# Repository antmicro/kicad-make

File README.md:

# KiCad Make (kmake)

Copyright (c) 2019-2026 [Antmicro](https://www.antmicro.com)

This is a simple utility that automates handling of [KiCad](https://www.kicad.org/) projects.
`kmake` provides a unified way to generate KiCad production files and manage project structure.
The script can be used locally and in conjunction with CI infrastructure.
`kmake` primarily targets KiCad 9 projects (supporting also KiCad 8-10).
It uses the KiCad CLI where possible and [askiff](https://github.com/antmicro/askiff) for functions that require raw file manipulation.

> KiCad 8 files should be fully supported (they will be upgraded on fly), however this has not been extensively tested.

## Documentation

Visit the [`kmake` documentation](https://antmicro.github.io/kicad-make/) for more information about usage and development of `kmake`.

## Installation

### Requirements

`kmake` depends on the following packages:

* `KiCad 9.0.x`
* `python >= 3.11`

### Installation (Debian)

1. Install requirements

    ```bash
    sudo apt install kicad python3 pipx
    pipx ensurepath
    ```

2. Clone and install `kmake` repository:

    ```bash
    pipx install 'git+https://github.com/antmicro/kicad-make.git'
    ```

## Usage

> Important: All commands should be issued from the KiCad project root directory.

To show available functionalities run:

```bash
cd <KiCad project directory>
kmake --help
```

## Version

As an convention, the `kmake` version is derived from the `KiCad` version supported by the release.
For example, `kmake` version `9.0.x` supports `KiCad` version `9.0.x`.

To check which version of `kmake` is installed in your system, run:

```bash
kmake version
```

## Licensing

This project is licensed under the [Apache-2.0](LICENSE) license.

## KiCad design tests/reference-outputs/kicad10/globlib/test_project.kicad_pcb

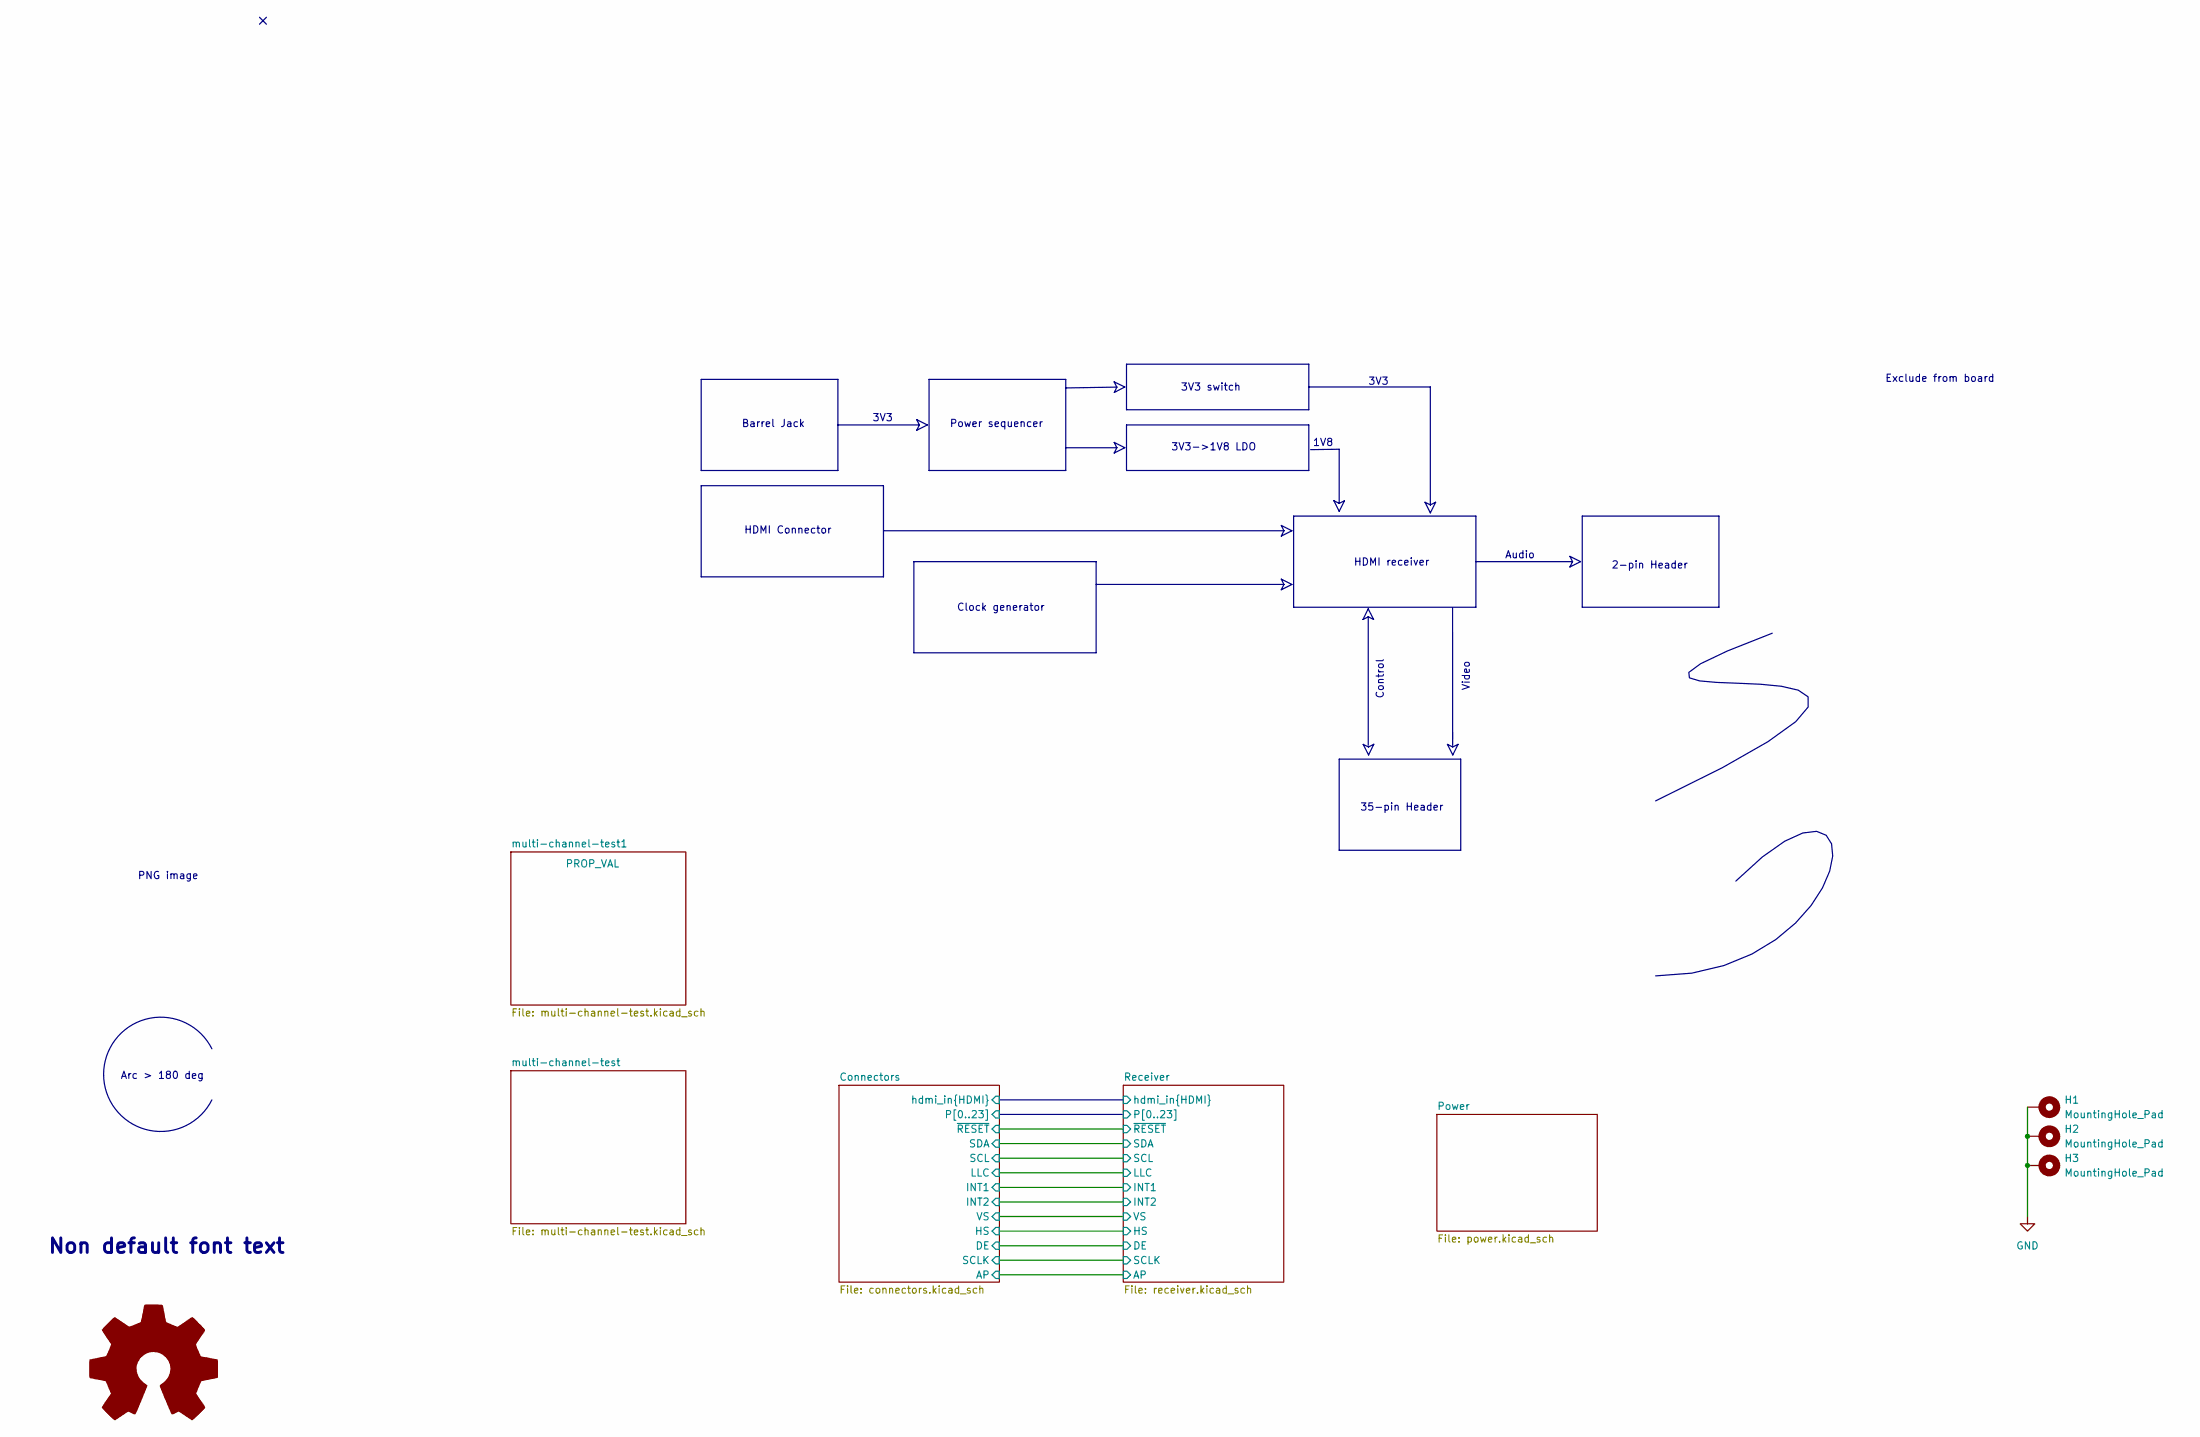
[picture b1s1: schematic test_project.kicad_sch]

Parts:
H1, H2, H3: MountingHole_Pad

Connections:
GND: H1.1, H2.1, H3.1; also elsewhere on the board

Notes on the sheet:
Control
Arc > 180 deg
PNG image
3V3
Video
1V8
Exclude from board
Audio
3V3 switch
Power sequencer
2-pin Header
35-pin Header
3V3->1V8 LDO
Barrel Jack
Non default font text
Clock generator
HDMI Connector
HDMI receiver

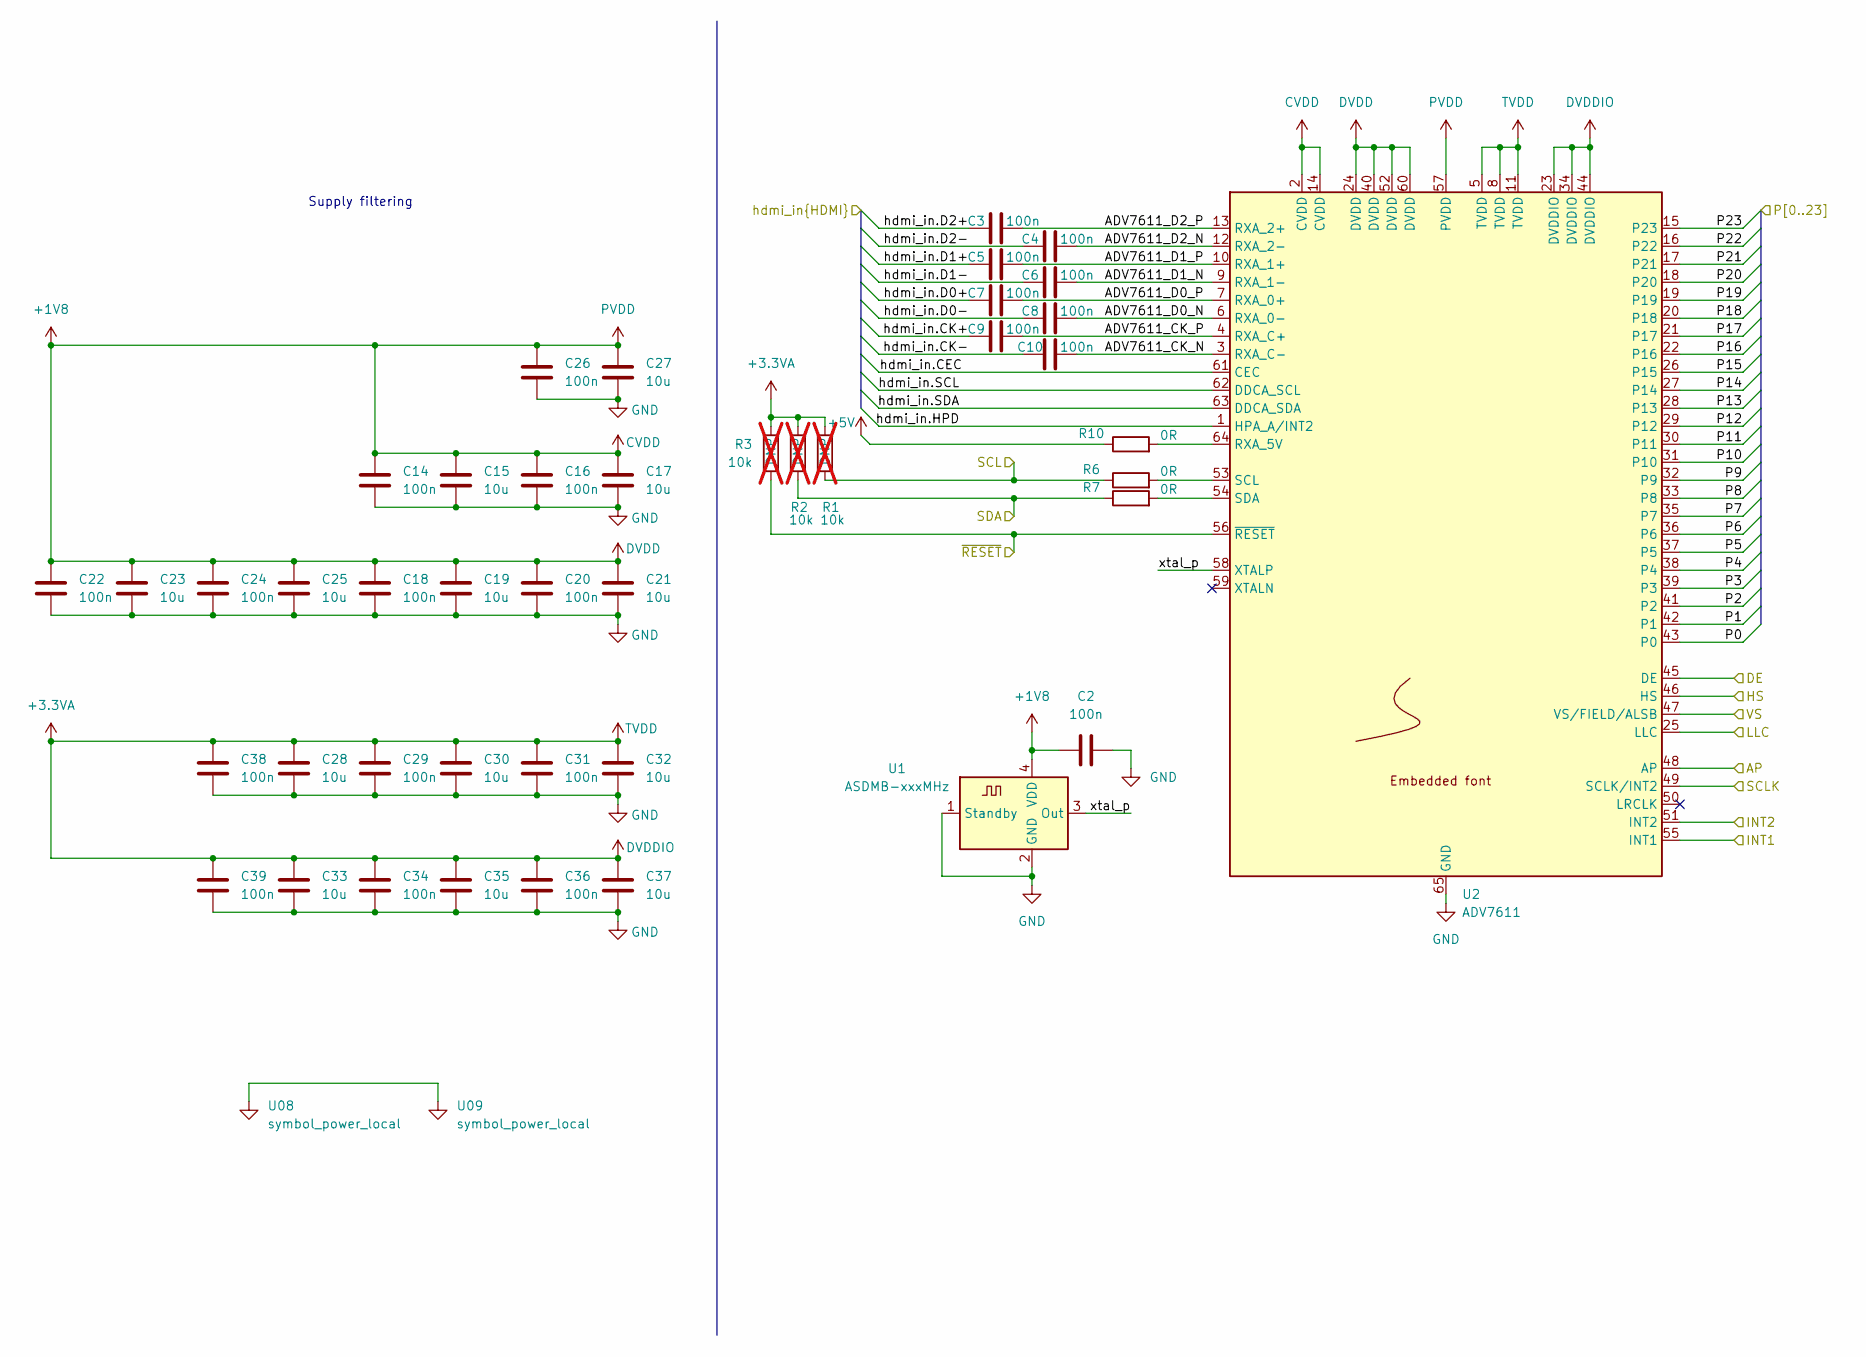
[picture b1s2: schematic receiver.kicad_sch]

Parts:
C2, C3, C4, C5, C6, C7, C8, C9, C10, C14, C16, C18, C20, C22, C24, C26, C29, C31, C34, C36, C38, C39: 100n
C15, C17, C19, C21, C23, C25, C27, C28, C30, C32, C33, C35, C37: 10u
R1, R2, R3: 10k; not fitted
R6, R7, R10: 0R
U1: ASDMB-xxxMHz; Oscillator_SMD_Abracon_ASDMB-4Pin_2.5x2.0mm; MPN ASDMB-28.6363MHz-XY
U2: ADV7611; LQFP-64-1EP_10x10mm_P0.5mm_EP5x5mm
U08, U09: symbol_power_local

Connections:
+1V8: C2.2, C14.1, C15.1, C16.1, C17.1, C18.1, C19.1, C20.1, C21.1, C22.1, C23.1, C24.1, C25.1, C26.1, C27.1, U1.4 (VDD), U2.2 (CVDD), U2.14 (CVDD), U2.24 (DVDD), U2.40 (DVDD), U2.52 (DVDD), U2.57 (PVDD), U2.60 (DVDD); also elsewhere on the board
+3.3VA: C28.1, C29.1, C30.1, C31.1, C32.1, C33.1, C34.1, C35.1, C36.1, C37.1, C38.1, C39.1, R1.1, R2.1, R3.1, U2.5 (TVDD), U2.8 (TVDD), U2.11 (TVDD), U2.23 (DVDDIO), U2.34 (DVDDIO), U2.44 (DVDDIO); also elsewhere on the board
+5V: R10.1; also elsewhere on the board
/Connectors/AP: U2.48 (AP); also elsewhere on the board
/Connectors/DE: U2.45 (DE); also elsewhere on the board
/Connectors/HS: U2.46 (HS); also elsewhere on the board
/Connectors/INT1: U2.55 (INT1); also elsewhere on the board
/Connectors/INT2: U2.51 (INT2); also elsewhere on the board
/Connectors/LLC: U2.25 (LLC); also elsewhere on the board
/Connectors/P0: U2.43 (P0); also elsewhere on the board
/Connectors/P1: U2.42 (P1); also elsewhere on the board
/Connectors/P2: U2.41 (P2); also elsewhere on the board
/Connectors/P3: U2.39 (P3); also elsewhere on the board
/Connectors/P4: U2.38 (P4); also elsewhere on the board
/Connectors/P5: U2.37 (P5); also elsewhere on the board
/Connectors/P6: U2.36 (P6); also elsewhere on the board
/Connectors/P7: U2.35 (P7); also elsewhere on the board
/Connectors/P8: U2.33 (P8); also elsewhere on the board
/Connectors/P9: U2.32 (P9); also elsewhere on the board
/Connectors/P10: U2.31 (P10); also elsewhere on the board
/Connectors/P11: U2.30 (P11); also elsewhere on the board
/Connectors/P12: U2.29 (P12); also elsewhere on the board
/Connectors/P13: U2.28 (P13); also elsewhere on the board
/Connectors/P14: U2.27 (P14); also elsewhere on the board
/Connectors/P15: U2.26 (P15); also elsewhere on the board
/Connectors/P16: U2.22 (P16); also elsewhere on the board
/Connectors/P17: U2.21 (P17); also elsewhere on the board
/Connectors/P18: U2.20 (P18); also elsewhere on the board
/Connectors/P19: U2.19; also elsewhere on the board
/Connectors/P20: U2.18 (P20); also elsewhere on the board
/Connectors/P21: U2.17 (P21); also elsewhere on the board
/Connectors/P22: U2.16 (P22); also elsewhere on the board
/Connectors/P23: U2.15 (P23); also elsewhere on the board
/Connectors/SCL: R1.2, R6.1; also elsewhere on the board
/Connectors/SCLK: U2.49 (SCLK/INT2); also elsewhere on the board
/Connectors/SDA: R2.2, R7.1; also elsewhere on the board
/Connectors/VS: U2.47 (VS/FIELD/ALSB); also elsewhere on the board
/Connectors/hdmi_in.CEC: U2.61 (CEC); also elsewhere on the board
/Connectors/hdmi_in.CK+: C9.1; also elsewhere on the board
/Connectors/hdmi_in.CK-: C10.1; also elsewhere on the board
/Connectors/hdmi_in.D0+: C7.1; also elsewhere on the board
/Connectors/hdmi_in.D0-: C8.1; also elsewhere on the board
/Connectors/hdmi_in.D1+: C5.1; also elsewhere on the board
/Connectors/hdmi_in.D1-: C6.1; also elsewhere on the board
/Connectors/hdmi_in.D2+: C3.1; also elsewhere on the board
/Connectors/hdmi_in.D2-: C4.1; also elsewhere on the board
/Connectors/hdmi_in.HPD: U2.1 (HPA_A/INT2); also elsewhere on the board
/Connectors/hdmi_in.SCL: U2.62 (DDCA_SCL); also elsewhere on the board
/Connectors/hdmi_in.SDA: U2.63 (DDCA_SDA); also elsewhere on the board
/Connectors/~RESET: R3.2, U2.56 (~RESET); also elsewhere on the board
/Receiver/ADV7611_CK_N: C10.2, U2.3 (RXA_C-)
/Receiver/ADV7611_CK_P: C9.2, U2.4 (RXA_C+)
/Receiver/ADV7611_D0_N: C8.2, U2.6 (RXA_0-)
/Receiver/ADV7611_D0_P: C7.2, U2.7 (RXA_0+)
/Receiver/ADV7611_D1_N: C6.2, U2.9 (RXA_1-)
/Receiver/ADV7611_D1_P: C5.2, U2.10 (RXA_1+)
/Receiver/ADV7611_D2_N: C4.2, U2.12 (RXA_2-)
/Receiver/ADV7611_D2_P: C3.2, U2.13 (RXA_2+)
/Receiver/xtal_p: U1.3 (Out), U2.58 (XTALP)
GND: C2.1, C14.2, C15.2, C16.2, C17.2, C18.2, C19.2, C20.2, C21.2, C22.2, C23.2, C24.2, C25.2, C26.2, C27.2, C28.2, C29.2, C30.2, C31.2, C32.2, C33.2, C34.2, C35.2, C36.2, C37.2, C38.2, C39.2, U1.1 (Standby), U1.2 (GND), U2.65 (GND); also elsewhere on the board
unnamed: R10.2, U2.64 (RXA_5V)
unnamed: R6.2, U2.53 (SCL)
unnamed: R7.2, U2.54 (SDA)
unnamed: U08., U09.

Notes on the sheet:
Supply filtering

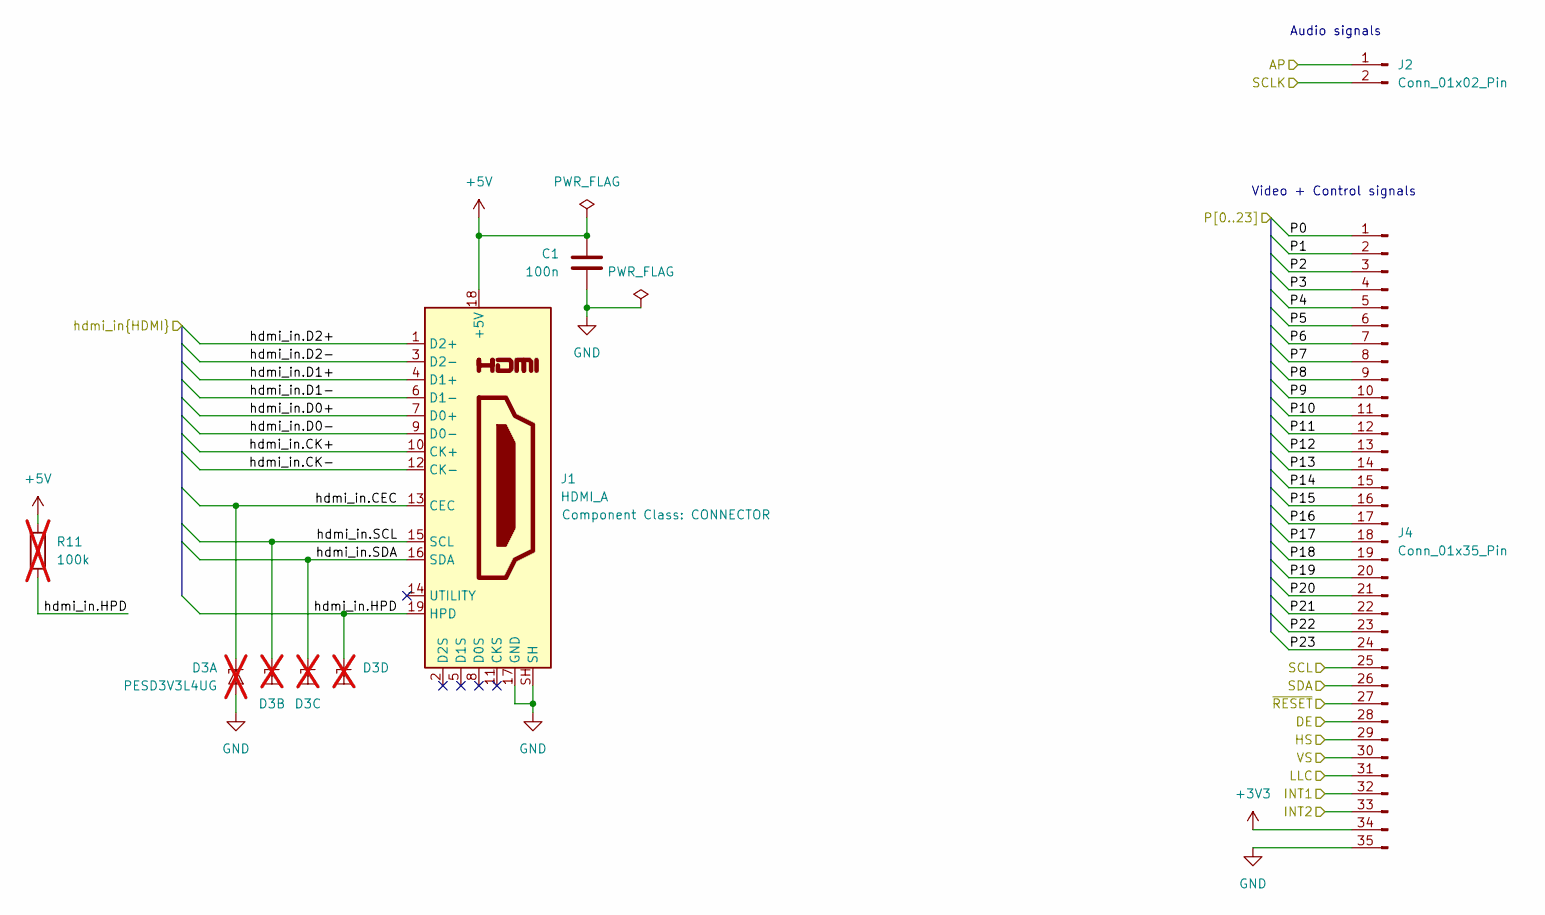
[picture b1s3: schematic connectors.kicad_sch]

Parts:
C1: 100n
D3: PESD3V3L4UG; SOT-353_SC-70-5; not fitted
J1: HDMI_A
J2: Conn_01x02_Pin
J4: Conn_01x35_Pin
R11: 100k; not fitted

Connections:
+3V3: J4.34; also elsewhere on the board
+5V: C1.1, J1.18 (+5V), R11.1; also elsewhere on the board
/Connectors/AP: J2.1; also elsewhere on the board
/Connectors/DE: J4.28; also elsewhere on the board
/Connectors/HS: J4.29; also elsewhere on the board
/Connectors/INT1: J4.32; also elsewhere on the board
/Connectors/INT2: J4.33; also elsewhere on the board
/Connectors/LLC: J4.31; also elsewhere on the board
/Connectors/P0: J4.1; also elsewhere on the board
/Connectors/P1: J4.2; also elsewhere on the board
/Connectors/P2: J4.3; also elsewhere on the board
/Connectors/P3: J4.4; also elsewhere on the board
/Connectors/P4: J4.5; also elsewhere on the board
/Connectors/P5: J4.6; also elsewhere on the board
/Connectors/P6: J4.7; also elsewhere on the board
/Connectors/P7: J4.8; also elsewhere on the board
/Connectors/P8: J4.9; also elsewhere on the board
/Connectors/P9: J4.10; also elsewhere on the board
/Connectors/P10: J4.11; also elsewhere on the board
/Connectors/P11: J4.12; also elsewhere on the board
/Connectors/P12: J4.13; also elsewhere on the board
/Connectors/P13: J4.14; also elsewhere on the board
/Connectors/P14: J4.15; also elsewhere on the board
/Connectors/P15: J4.16; also elsewhere on the board
/Connectors/P16: J4.17; also elsewhere on the board
/Connectors/P17: J4.18; also elsewhere on the board
/Connectors/P18: J4.19; also elsewhere on the board
/Connectors/P19: J4.20; also elsewhere on the board
/Connectors/P20: J4.21; also elsewhere on the board
/Connectors/P21: J4.22; also elsewhere on the board
/Connectors/P22: J4.23; also elsewhere on the board
/Connectors/P23: J4.24; also elsewhere on the board
/Connectors/SCL: J4.25; also elsewhere on the board
/Connectors/SCLK: J2.2; also elsewhere on the board
/Connectors/SDA: J4.26; also elsewhere on the board
/Connectors/VS: J4.30; also elsewhere on the board
/Connectors/hdmi_in.CEC: D3.1 (K1), J1.13 (CEC); also elsewhere on the board
/Connectors/hdmi_in.CK+: J1.10 (CK+); also elsewhere on the board
/Connectors/hdmi_in.CK-: J1.12 (CK-); also elsewhere on the board
/Connectors/hdmi_in.D0+: J1.7 (D0+); also elsewhere on the board
/Connectors/hdmi_in.D0-: J1.9 (D0-); also elsewhere on the board
/Connectors/hdmi_in.D1+: J1.4 (D1+); also elsewhere on the board
/Connectors/hdmi_in.D1-: J1.6 (D1-); also elsewhere on the board
/Connectors/hdmi_in.D2+: J1.1 (D2+); also elsewhere on the board
/Connectors/hdmi_in.D2-: J1.3 (D2-); also elsewhere on the board
/Connectors/hdmi_in.HPD: D3.5 (K4), J1.19 (HPD), R11.2; also elsewhere on the board
/Connectors/hdmi_in.SCL: D3.3 (K2), J1.15 (SCL); also elsewhere on the board
/Connectors/hdmi_in.SDA: D3.4 (K3), J1.16 (SDA); also elsewhere on the board
/Connectors/~RESET: J4.27; also elsewhere on the board
GND: C1.2, D3.2 (A), J1.17 (GND), J1.SH, J4.35; also elsewhere on the board

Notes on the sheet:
Audio signals
Video + Control signals

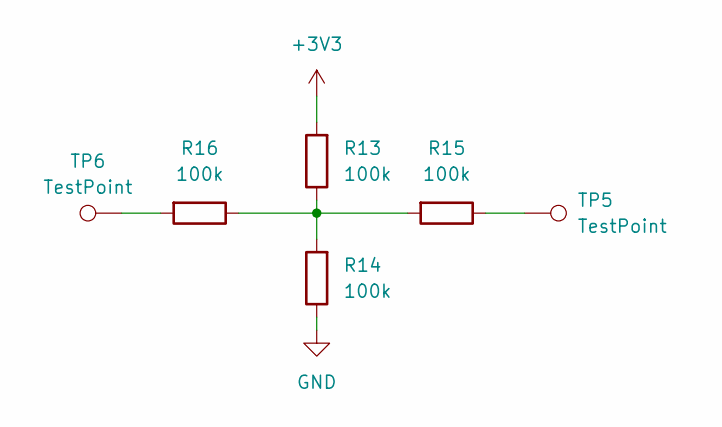
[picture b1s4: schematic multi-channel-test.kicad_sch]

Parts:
R13, R14, R15, R16: 100k
TP5, TP6: TestPoint

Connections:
+3V3: R13.2; also elsewhere on the board
GND: R14.1; also elsewhere on the board
unnamed: R13.1, R14.2, R15.2, R16.1
unnamed: R15.1, TP5.1
unnamed: R16.2, TP6.1

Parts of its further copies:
R17, R18, R19, R20: 100k
TP7, TP8: TestPoint

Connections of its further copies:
+3V3: R18.2; also elsewhere on the board
GND: R19.1; also elsewhere on the board
unnamed: R17.1, R18.1, R19.2, R20.2
unnamed: R17.2, TP7.1
unnamed: R20.1, TP8.1

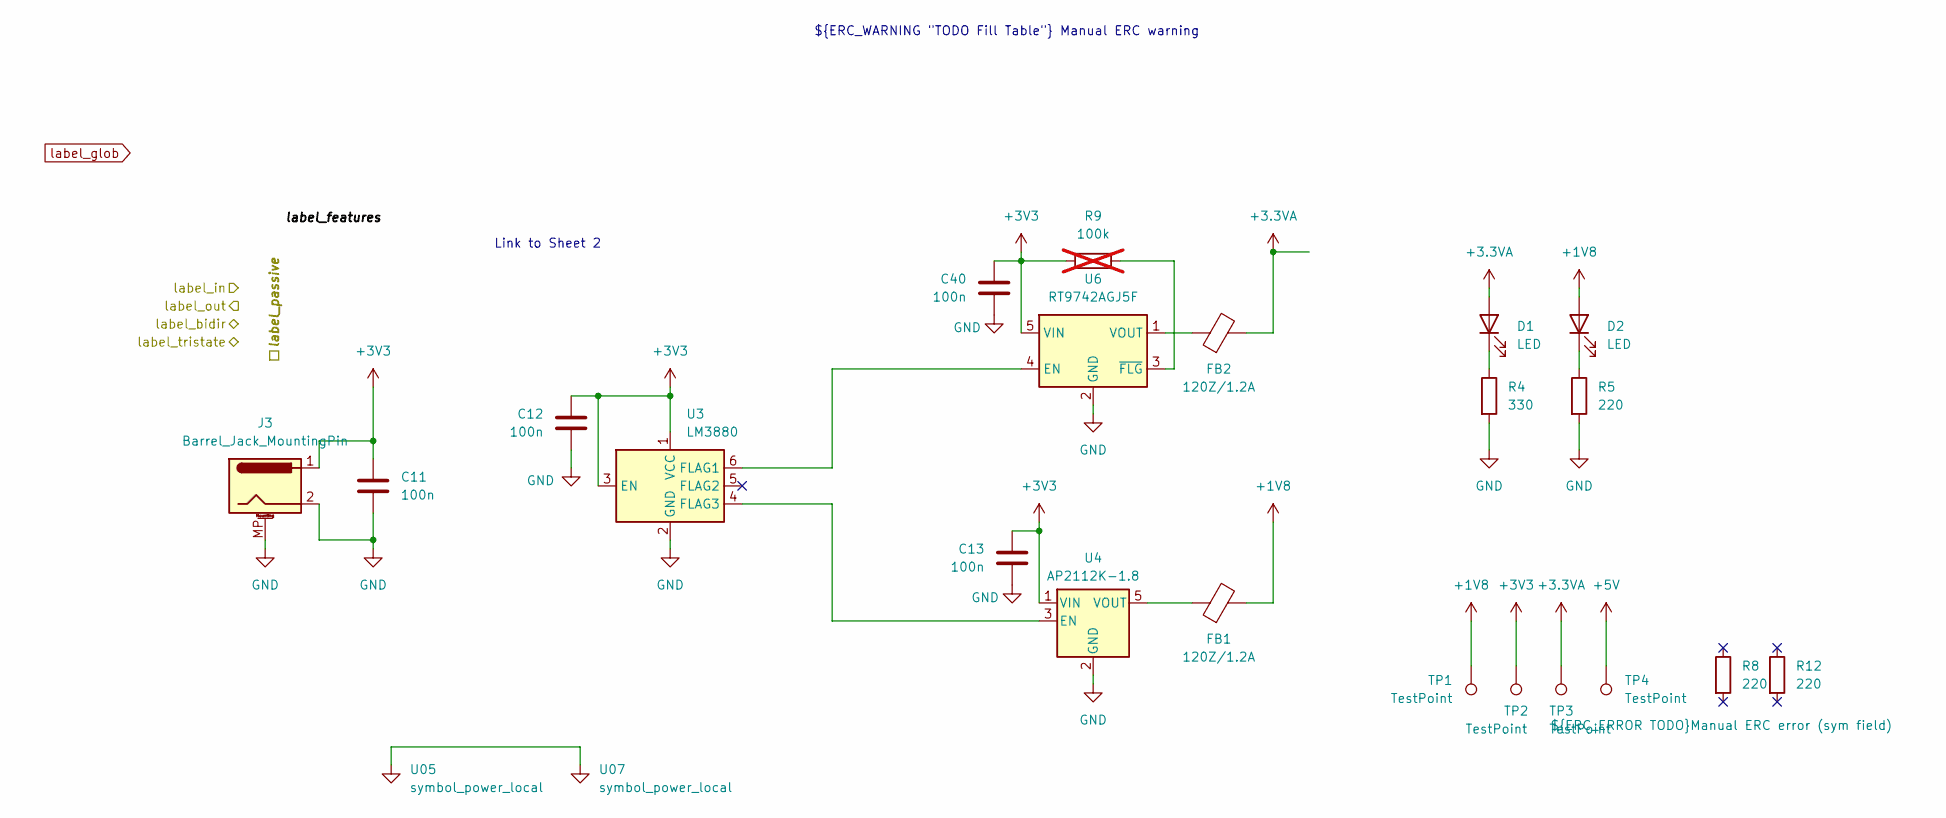
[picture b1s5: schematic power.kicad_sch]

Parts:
C11, C12, C13, C40: 100n
D1, D2: LED
FB1, FB2: 120Z/1.2A
J3: Barrel_Jack_MountingPin
R4: 330
R5, R8, R12: 220
R9: 100k; not fitted
TP1, TP2, TP3, TP4: TestPoint
U3: LM3880; SOT-23-6
U4: AP2112K-1.8; SOT-23-5
U05, U07: symbol_power_local
U6: RT9742AGJ5F; TSOT-23-5

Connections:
+1V8: D2.2 (A), FB1.2, TP1.1; also elsewhere on the board
+3.3VA: D1.2 (A), FB2.2, TP3.1; also elsewhere on the board
+3V3: C11.1, C12.2, C13.2, C40.2, J3.1, R9.1, TP2.1, U3.1 (VCC), U3.3 (EN), U4.1 (VIN), U6.5 (VIN); also elsewhere on the board
+5V: TP4.1; also elsewhere on the board
GND: C11.2, C12.1, C13.1, C40.1, J3.2, J3.MP (MountPin), R4.2, R5.2, U3.2 (GND), U4.2 (GND), U6.2 (GND); also elsewhere on the board
unnamed: D1.1 (K), R4.1
unnamed: D2.1 (K), R5.1
unnamed: U3.6 (FLAG1), U6.4 (EN)
unnamed: U3.4 (FLAG3), U4.3 (EN)
unnamed: FB1.1, U4.5 (VOUT)
unnamed: U05., U07.
unnamed: FB2.1, U6.1 (VOUT)
unnamed: R9.2, U6.3 (~FLG)

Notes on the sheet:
Link to Sheet 2
${ERC_WARNING "TODO Fill Table"} Manual ERC warning

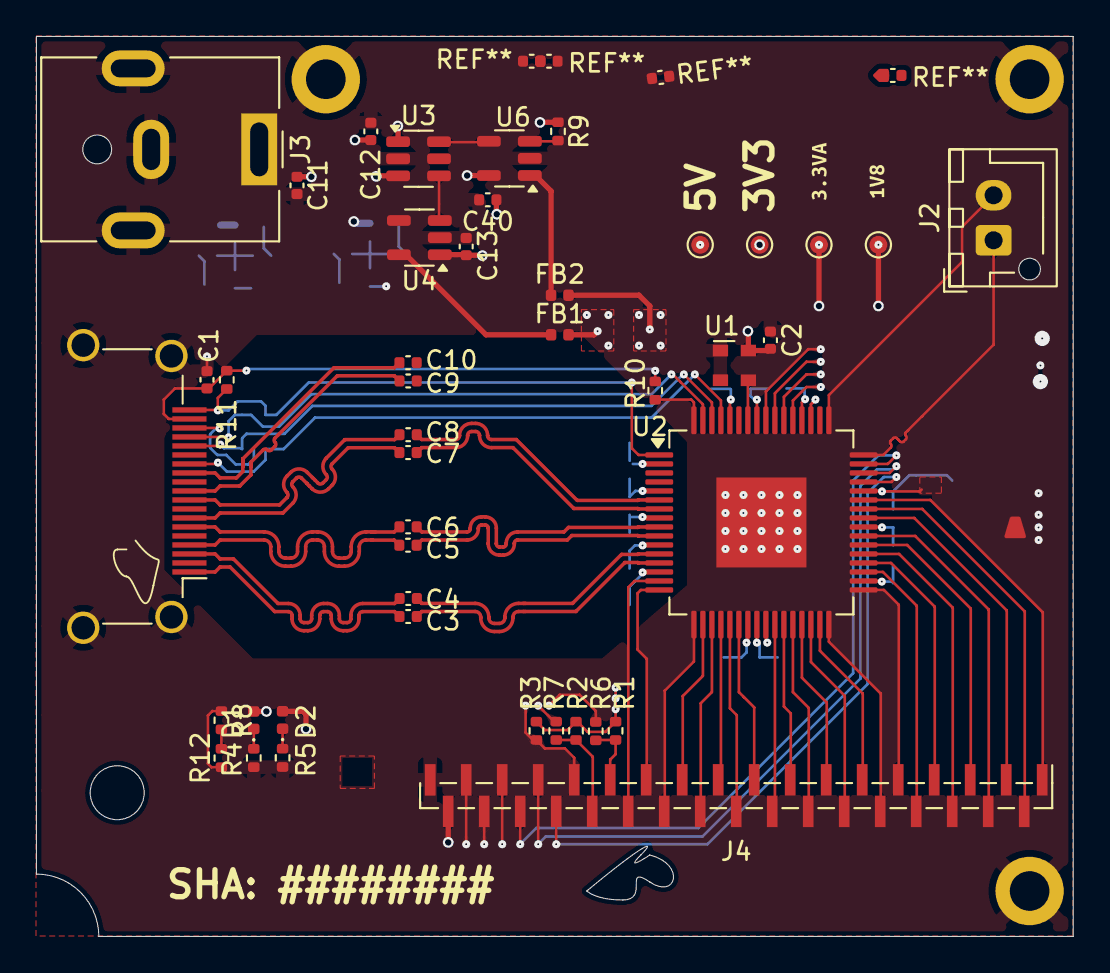
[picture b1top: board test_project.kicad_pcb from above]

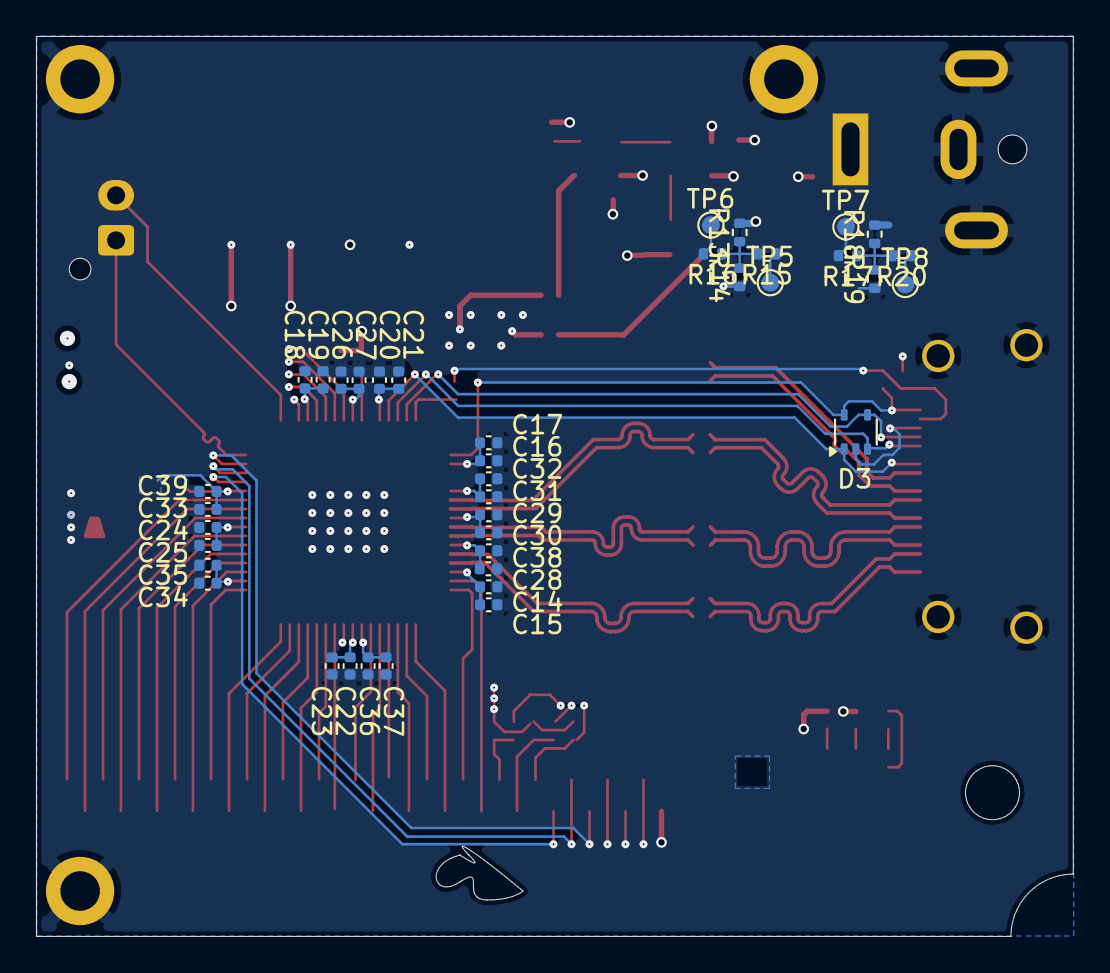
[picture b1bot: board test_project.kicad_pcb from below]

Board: 8 copper layers, 57.6 x 50.0 mm, 87 parts (39 on the bottom side), 77 nets.

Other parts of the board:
kibuzzard-67891633: G***; kibuzzard-67891633
kibuzzard-67891646: G***; kibuzzard-67891646

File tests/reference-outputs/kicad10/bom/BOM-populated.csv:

"Reference","Quantity","Value","Footprint","Manufacturer","MPN"
"C1 C2 C3 C4 C5 C6 C7 C8 C9 C10 C11 C12 C13 C14 C16 C18 C20 C22 C24 C26 C29 C31 C34 C36 C38 C39 C40","27","100n","C_0402_1005Metric","",""
"C15 C17 C19 C21 C23 C25 C27 C28 C30 C32 C33 C35 C37","13","10u","C_0402_1005Metric","",""
"D1 D2","2","LED","LED_0402_1005Metric","",""
"FB1 FB2","2","120Z/1.2A","L_0402_1005Metric","",""
"J1","1","HDMI_A","HDMI_A_Amphenol_10029449-x01xLF_Horizontal","",""
"J2","1","Conn_01x02_Pin","JST_XH_B2B-XH-AM_1x02_P2.50mm_Vertical","",""
"J3","1","Barrel_Jack_MountingPin","BarrelJack_CUI_PJ-063AH_Horizontal","",""
"J4","1","Conn_01x35_Pin","PinHeader_1x35_P1.00mm_Vertical_SMD_Pin1Left","",""
"R4","1","330","R_0402_1005Metric","",""
"R5 R8 R12","3","220","R_0402_1005Metric","",""
"R6 R7 R10","3","0R","R_0402_1005Metric","",""
"R13 R14 R15 R16","4","100k","R_0402_1005Metric","",""
"U1","1","ASDMB-xxxMHz","Oscillator_SMD_Abracon_ASDMB-4Pin_2.5x2.0mm","","ASDMB-28.6363MHz-XY"
"U2","1","ADV7611","LQFP-64-1EP_10x10mm_P0.5mm_EP5x5mm","",""
"U3","1","LM3880","SOT-23-6","",""
"U4","1","AP2112K-1.8","SOT-23-5","",""
"U6","1","RT9742AGJ5F","SOT-23-5","",""

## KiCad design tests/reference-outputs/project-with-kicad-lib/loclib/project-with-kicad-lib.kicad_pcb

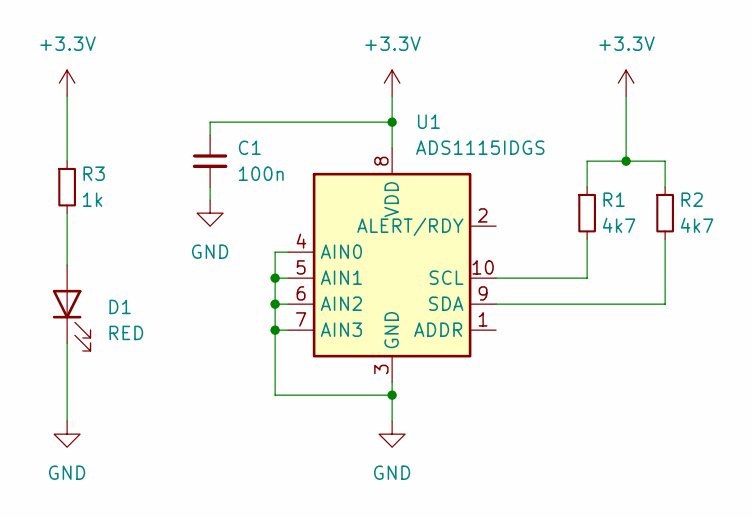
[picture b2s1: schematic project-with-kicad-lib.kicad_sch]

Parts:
C1: 100n; C_0402_1005Metric_Pad0.74x0.62mm_HandSolder
D1: RED; LED_D5.0mm
R1, R2: 4k7; R_0402_1005Metric_Pad0.72x0.64mm_HandSolder
R3: 1k; R_0402_1005Metric_Pad0.72x0.64mm_HandSolder
U1: ADS1115IDGS; TSSOP-10_3x3mm_P0.5mm

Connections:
+3V3: C1.1, R1.1, R2.1, R3.1, U1.8 (VDD)
GND: C1.2, D1.1 (K), U1.3 (GND), U1.4 (AIN0), U1.5 (AIN1), U1.6 (AIN2), U1.7 (AIN3)
unnamed: D1.2 (A), R3.2
unnamed: R1.2, U1.10 (SCL)
unnamed: R2.2, U1.9 (SDA)

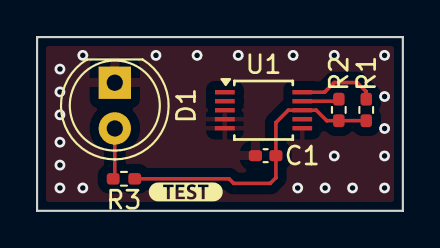
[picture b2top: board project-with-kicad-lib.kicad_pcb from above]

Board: 2 copper layers, 20.3 x 9.7 mm, 7 parts (0 on the bottom side), 5 nets.

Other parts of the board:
kibuzzard-66D96414: G***; kibuzzard-66D96414

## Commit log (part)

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2024-05-23 update 10ffda3ef29a9792a9e7605f11651d114f26322d
2024-07-30 Docs: do not generate the pdf button
2024-08-05 [#59870] gerbers: remove gerber renaming in favor of kicad-cli arg
2024-08-05 [#59481] Remove `blend-check` from CI
2024-08-05 [#60273] rename: Stop adding empty lines
2024-08-05 Enable documentation-release as test
2024-08-05 [#58706] tests: Add test for netlist
    [#58706] tests: Move setUp to top
    [#58706] tests: Add docstrings
    [#58706] tests: Add netlist to reference output
    [#58706] tests: Remove unused code
    [#58706] tests: Reformat code
    [#58706] tests: Use variables instead of hardcoded paths
2024-08-05 [#62570] dnp: new flag: add paste on tht
2024-08-05 [#57415] Install default logos
2024-08-05 [#61748] Add information about updating pip
2024-08-05 [#66186] Remove handle_web_width_bug check
2024-08-05 [#61938] Wireframe fix
2024-08-05 [#61938] Bump KiUtils version
2024-08-05 [#62103] pyproject: add dynamic versioning
2024-08-05 [#59183] Replace distutils with sysconfig
2024-08-05 [#57612] Fix loclib -c causing segfault
2024-08-07 [#63762] Update CircuitHub BOM headers and DNP field content
2024-08-07 [#63765] DNP: Fix handling schematic copies
2024-08-08 [#62578] Add test project for loclib and globlib
2024-08-14 [#63603] Update devel docs
2024-08-16 [#64100] globlib: Do not edit PCB when -s switch is set
2024-08-20 [#60106] wireframe: change layers
2024-08-21 [#63388] tests: Add tests for loclib
2024-08-21 [#64047] Add schematic name to sch command
2024-08-27 [#64397] Fix kicad-cli handling in kmake_helper
2024-09-03 [#62578] tests: Add tests for globlib
2024-09-05 [#64144] Bump kiutils to d3a11a5
2024-09-06 [#63381] Add kibuzzard-to-graphic command
2024-09-11 Add automation
2024-09-13 update 08a94338fee71b7007b8f91b62e18f9264ed4980
2024-09-25 [#66059] Expand wireframe cmd to cover assembly drawing
2024-10-02 [#64032] Remove DNP property
2024-10-14 [#66875] Add prettifiy command
2024-10-17 [#67443] Minor fixes & improvements for tests
2024-10-17 [#67443] Add migrate_project script
2024-10-17 [#67443] Create base class for tests; Migrate tests to it
2024-10-17 [#67443] Move project_migration inside KmakeTestCase
2024-10-22 [#67645] Fix sublayer export
2024-10-23 Update CI
2024-11-05 [#68292] Update docker registry organization
2024-11-06 [#68292] CI: fix tests on main
2024-11-06 [#68292] Update image selection handling
2024-11-06 [#68292] CI: skip clonning repo in deploy jobs
2024-11-07 [#68292] CI: suffix images with -testing only; rebuild on deploy
2024-11-08 [#65423] Kmake for KiCad 8
2024-11-08 [#68153] Update docs and checks to kicad8
2024-11-11 [#67579] Add test_project with KiCad 8 features
2024-11-12 [#66803] gerber: Clip silkscreen by default
2024-11-13 [#67322] Add version subcmd
2024-11-13 [#67322] Add version cmd test
2024-11-15 [#68838] Add features to readme
2024-11-18 [#67440] Update bom.py
2024-11-18 [#67440] Update gerbers.py
2024-11-18 [#67440] Add whitespace test
2024-11-18 [#67440] Update impedance_map.py
2024-11-26 [DEV]: CI: remove allow-to-fail
2024-11-29 [#69508] dnp: Fix --list-broken modifying files
2024-11-29 Apply suggestion to .ci.yml
2024-11-29 [#69504] CI: run deploy-docs on all branches
2024-12-03 README: Update overview and licensing section
2024-12-03 Docs: specify sphinx variant
2024-12-03 update c5080211a25a3681d148da90bce169ca2bb5997d
2024-12-04 Notes added by 'git notes add'
2024-12-11 Add layer user names to stackup-export
2025-01-27 [#68432] Add design errors to PCB
2025-01-27 [#71761] aux-origin: Cover circular edge cuts
2025-01-27 [#71536] Fix pip install in docs
2025-01-27 [#71777] aux-origin: simplify functions args
2025-01-27 [#71777] aux-origin: Remove redundant nesting
2025-01-27 [#71777] Aux origin edge shapes
2025-01-27 [#71105] Add missing gitignore from GitHub template
2025-01-27 [#71105] Except stackup.csv
2025-01-27 [#71105] Update stackup exception
2025-01-27 [#71105] Ignore kicad_sym_bak
2025-01-27 [#71105] Except python related files
2025-01-27 [#71105] Except exports from Antmicro's tools
2025-01-27 [#71105] Add mechanical design files to gitignore
2025-01-29 [#70870] ci.yml: Remove debug stage
2025-01-29 [#70870] loclib: Fix linting
2025-02-13 Fix deploying docs
2025-02-17 [#71014] Bump kiutils commit
2025-02-26 [#73645] impedance-map: fix for netclasses with regex
2025-03-21 [#68485] pcb-filter: handle components that are on both sides
2025-03-21 [#68485] wireframe: descriptions: ise User.Eco* layers
2025-03-21 [#68485] pcb-filter: fix reversed logic
2025-03-21 [#70013] wireframe: use argparse dafault feature insted of explicit asign
2025-03-21 [#68485] wireframe: add generate-frame option- generate expanded outline bbox
2025-03-21 [#70013] wireframe: change how args to pcb-filter are passed
2025-03-21 [#68485] pcb-filter: fix ref-filter
2025-03-21 [#68485] wireframe: unify edge.cuts width; mirror bottom
2025-03-21 [#68485] wireframe: better option descriptions
2025-03-21 [#68485] pcb-filter: fix keep_edge
2025-03-21 [#68485] wireframe: standardize main dimensions
2025-03-21 [#68485] wireframe: add pcb-filter-args-append option
2025-03-21 [#68485] wireframe: prefix file with `wireframe_`
2025-03-21 [#68485] wireframe: update justification of mirrored text
2025-03-21 [#68485] wireframe: fix pcb-filter-arg is None
2025-03-21 [#68485] pcb-filter: fix fp.angle==None
2025-03-21 [#68485] wireframe: pass args for pcb-filter
2025-03-21 [#68485] wireframe: move board modification to pcb-filter
2025-03-21 [#68485] pcb-filter: remove unnecessary print
2025-03-21 Fix CI
2025-03-21 Workflows: update action version
2025-03-21 update 7088c3aac8cecc253f533aed79b6d550975b7f9a
2025-04-07 [#75711] wireframe: Fix layer variables substitution
2025-04-14 [#75904] Fix resolving of KiCad Library variables
2025-06-02 [#75441] Kicad9
2025-06-02 [#78355] Kicad9 docs
2025-06-10 fixing cfg file reading
2025-06-10 [#78758] Use kicad9 in Github workflow
2025-06-11 update b9186b73ab40b8d4d3f5220b8386657430644699
2025-06-13 Bump python requirement
2025-07-07 [#79606] Fix layers keyword
2025-07-29 [#80792] pcb_filter: Add flag to filter footprint pads
2025-08-06 [#81489] Update kiutils Polygons
2025-08-11 [#81447] Update ci template
2025-09-04 BOM: Fix blacklist corner case
2025-09-22 Reduce ambiguity in tests
2025-10-06 [#84583] Update tests for Kicad 9.0.5
2025-10-06 [#84800] Wireframe: restore DNP crossout
2025-10-06 [#84800] Wireframe: filter out fp with N* designators
2025-10-23 DNP: return early with info message if nothing to do
2025-10-23 DNP: Update test
2025-11-12 globlib: more robust MPN matching
2025-11-13 [#86870] Bump kiutils
2025-11-13 [#86870] Fix max line length exceeded
2025-11-21 [#87089] dnp: support sheet level dnp
2025-11-21 [#87089] Remove unused imports
2025-11-28 Bump kiutils
2025-12-31 [#87092] Handle Edge.Cuts layer of rotated footprints
2026-01-15 [#89119] wireframe: Change drill marks on SVG output
2026-01-15 [#89119] wireframe: Allow only svg or gerber output
2026-01-15 [#89119] pcb_filter: Serialization fix
2026-01-15 [#89119] pcb-filter: move layer filtration to function
2026-01-15 [#89119] pcb-filter: simplify graphics standardization
2026-01-15 [#89119] pcb-filter: shove dimmensions when resizing them
2026-01-15 [#89119] pcb-filter: correct graphics stnadardization
2026-01-15 [#89119] wireframe: update dimensions layer filter
2026-01-15 [#89119] pcb_filter: Support empty ref filter
2026-01-15 [#89119] pcb-filter: change line thickness in std-graphics
2026-01-15 [#89119] pcb-filter: add graphics standardization
2026-01-15 [#89119] pcb-filter: shove dimmensions based on layer
2026-01-19 [#87086] Set black to 25.12.0 version
2026-01-21 [#90236] bom: correct grouping with --all
2026-01-21 [#90236] Remove unused dependencies
2026-01-30 [#90766] dnp: Do not touch in-bom property
2026-01-30 [#90766] dnp: fix test
2026-03-03 Fix prettify spelling
2026-03-05 [#92089] Dnp update behavior
2026-03-05 Add 2026 to copyright
2026-03-09 [#92092] Gerber add paste modifications
2026-03-09 Set variable for aperture command
2026-03-27 [#92092] Remove obsolete paste functionality
2026-04-01 [#68432] Add kmake drc and erc
2026-04-02 Revert to kicad 9.0.7
2026-04-02 bom: Honour Exclude from BOM
2026-04-02 bom: fix formatting
2026-04-03 [#94483] CI: Use main KiCad 9 image
2026-04-08 [#94517] Add askiff dependency
2026-04-08 [#94517] clean: allow instances with empty project name
2026-04-08 [#94517] clean: reword message
2026-04-08 [#94517] clean: save schematics after cleanup
2026-04-08 [#94517] test_project: update lib-tables
2026-04-10 [#94716] Updated askiff names
2026-04-10 [#94512] Remove coloredlogs
2026-04-17 Correct license
2026-04-17 [#94512] CI: Add template support
2026-04-17 [#94512] CI: correct template copy
2026-04-17 [#94512] check: start spell checks implementation
2026-04-17 [#94512] check: implement result printing for spell check
2026-04-17 [#94512] check: Improve spell check
2026-04-17 [#94512] check: Expand spell check to TitleBlock
2026-04-17 [#94512] Fix Dockerfile
2026-04-17 [#94512] spell-check: move cgroupfs-mount to script
2026-04-17 [#94512] spell-check: fix subcommand check
2026-04-17 [#94512] check spell: allow prinitng unknown to console
2026-04-17 [#94512] Skip template copy
2026-04-17 [#94512] spell-check: support ordinary text file input
2026-04-17 [#94512] spell-check: install apt packages in before_get_sources
2026-04-17 [#94512] check: require subcommand
2026-05-04 [#96108] Fix askiff field name
2026-05-04 [#94415] loclib: fix fp-lib-table quoting
2026-05-04 [#94415] loclib: replace kiutils with askiff
2026-05-04 [#93040] Move to askiff pcb files management; Sort imports
2026-05-04 [#93040] Use askiff for sch management
2026-05-04 [#93586] kibuzzard_to_graphics: migrate to askiff
2026-05-04 [#93040] globlib: lazy load global footprints
2026-05-04 [#93040] pnp: fix wrong field
2026-05-04 Bump to newest askiff - auxorigin
2026-05-04 [#93040] Update Readme
2026-05-04 [#93040] Unify variable name for project variable
2026-05-04 Port init_project wip
2026-05-04 Bump to newest askiff - bom
2026-05-04 Port pcb_filter wip
2026-05-04 [#94415] loclib: relay more on askiff impl
2026-05-04 [#93040] Fix globlib & wireframe
2026-05-04 [#93586] prettify: migrate to askiff
2026-05-04 [#93040] bom: use Path, remove typing_extensions
2026-05-04 Port gerbers.py
2026-05-04 [#93040] gerbers: switch to askiff pcb handling
2026-05-04 [#93040] Kicad_project: remove unnecessary functions and fields
2026-05-04 [#93040] stackup-export: update migrate to askiff
2026-05-04 [#93586] init_project/version: migrate to askiff
2026-05-04 [#93040] globlib: migrate to askiff
2026-05-04 [#93040] Fix issues from tests
2026-05-04 [#94716] Updated askiff class naming
2026-05-04 [#93040] impedance: finish askiff integration
2026-05-04 Port pnp.py
2026-05-04 Port auxorigin.py
2026-05-04 Port stackup_export.py
2026-05-04 [#93040] Restore legacy property handlers for tests
2026-05-04 Bump to newest askiff - clean
2026-05-04 [#95581] set_drc/dru: migrate to askiff
2026-05-04 [#93040] auxorigin: migrate to askiff
2026-05-04 Update globlib (sch missing)
2026-05-04 [#94415] loclib: format with black
2026-05-04 [#93040] Restore old stackup keys
2026-05-04 Port step.py
2026-05-04 Port impedance map attempt
2026-05-04 [#93040] Further integration of askiff Project fields
2026-05-04 [#93040] Correct field names
2026-05-04 [#93040] dnp: migrate to askiff
2026-05-04 [#93040] askiff: path->fs_path
2026-05-04 Port wireframe.py
2026-05-04 Port dnp.py
2026-05-04 [#93040] remove redundant code from kicad_project
2026-05-04 [#93040] Tests: Correct Legacy KiCadProject initialization
2026-05-04 [#93040] Update askiff hierarchy; silence type checks
2026-05-04 [#94415] loclib: remove unused variable
2026-05-04 Port kibuzzard_to_graphic
2026-05-04 [#93040] Fixes after review
2026-05-08 [#93049] Update CI
2026-05-13 [#93049] Update tests to use askiff
2026-05-18 [#93049] tests: Use askiff test project

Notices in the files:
parts and their libraries:
License: Apache-2.0
